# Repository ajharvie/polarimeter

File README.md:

Firmware and supporting data for a polarimeter as described in Scientific Reports: **A high-resolution polarimeter formed from inexpensive optical parts** https://doi.org/10.1038/s41598-020-61715-7

Code for the microcontroller can be found in the "Arduino Code" folder. The folder "Frontend tool" provides a simple python GUI for interfacing with the polarimeter. 
"Design files" contains .stl format files for custom parts used to build the polarimeter, as well as .brd files for circuit boards.
"Supporting Files" contains code for recording optical signals and simulating polarimeter behaviour, as well as data files for the plots presented in the paper.

*A.J. Harvie, T.W. Phillips and J.C. deMello*

**A new version - OPol - has been released. You can find the design files here: https://github.com/OpenPolarimeter/OPol, and a publication describing its build and use here: https://doi.org/10.1002/cmtd.202000057**

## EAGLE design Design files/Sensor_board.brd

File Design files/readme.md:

Design files for custom parts for the polarimeter, including:

1) .stl format files for the flow cell and mounting block
2) .stl format file for the 3d printed part for mounting the optical sensors onto an optical post
3) .brd and .sch files for a PCB to interface with the OPT101s (use of 8-pin DIP sockets recommended)
4) .stl format file for the 3d printed part for mounting the microcontroller
5) .brd and .sch files for a PCB for connections to the µC (and power passthrough)
6) A technical drawing of the flow cell dimensions

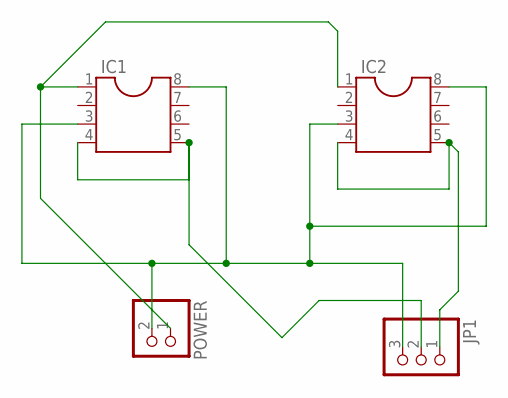
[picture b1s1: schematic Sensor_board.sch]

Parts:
IC1, IC2: DIL8S; SOCKET-08
JP1: PINHD-1X3; 1X03
POWER: PINHD-1X2; 1X02

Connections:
unnamed: IC1.3, IC1.8, IC2.3, IC2.8, JP1.3, POWER.2
unnamed: IC1.1, IC2.1, POWER.1
unnamed: IC1.4, IC1.5, JP1.2
unnamed: IC2.4, IC2.5, JP1.1

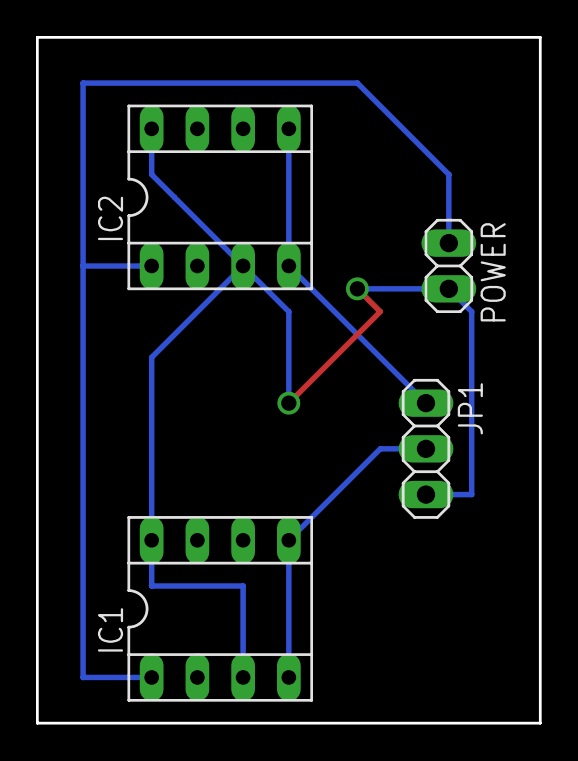
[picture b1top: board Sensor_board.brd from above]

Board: 2 copper layers, 27.9 x 38.1 mm, 4 parts (0 on the bottom side), 4 nets.

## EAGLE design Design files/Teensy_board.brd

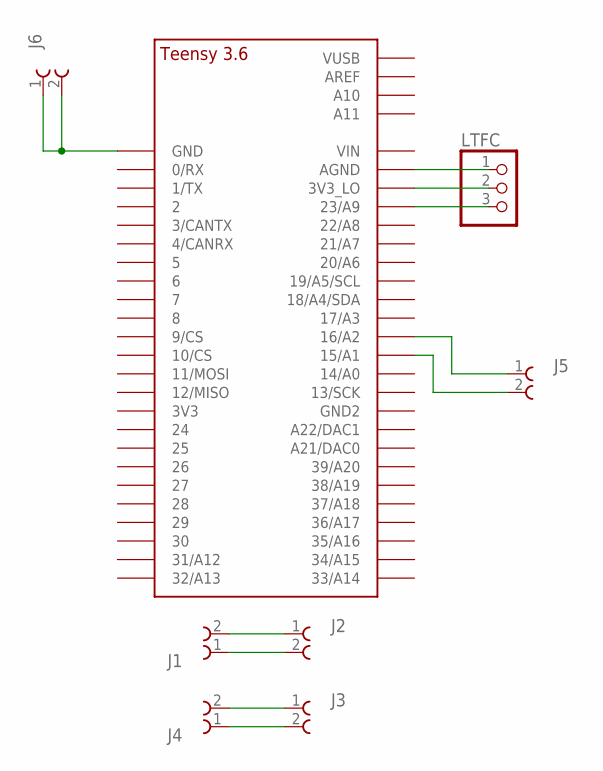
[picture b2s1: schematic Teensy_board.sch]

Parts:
J1, J2, J3, J4, J5, J6: 691103110002
LTFC: PINHD-1X3; 1X03
U$1: TEENSY_3.5/3.6_BASIC

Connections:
unnamed: LTFC.1, U$1.AGND
unnamed: LTFC.2, U$1.3V3_LO
unnamed: LTFC.3, U$1.23/A9
unnamed: J5.2, U$1.15/A1
unnamed: J5.1, U$1.16/A2
unnamed: J1.2, J2.1
unnamed: J1.1, J2.2
unnamed: J3.1, J4.2
unnamed: J3.2, J4.1
SIGNAL_G: J6.1, J6.2, U$1.GND

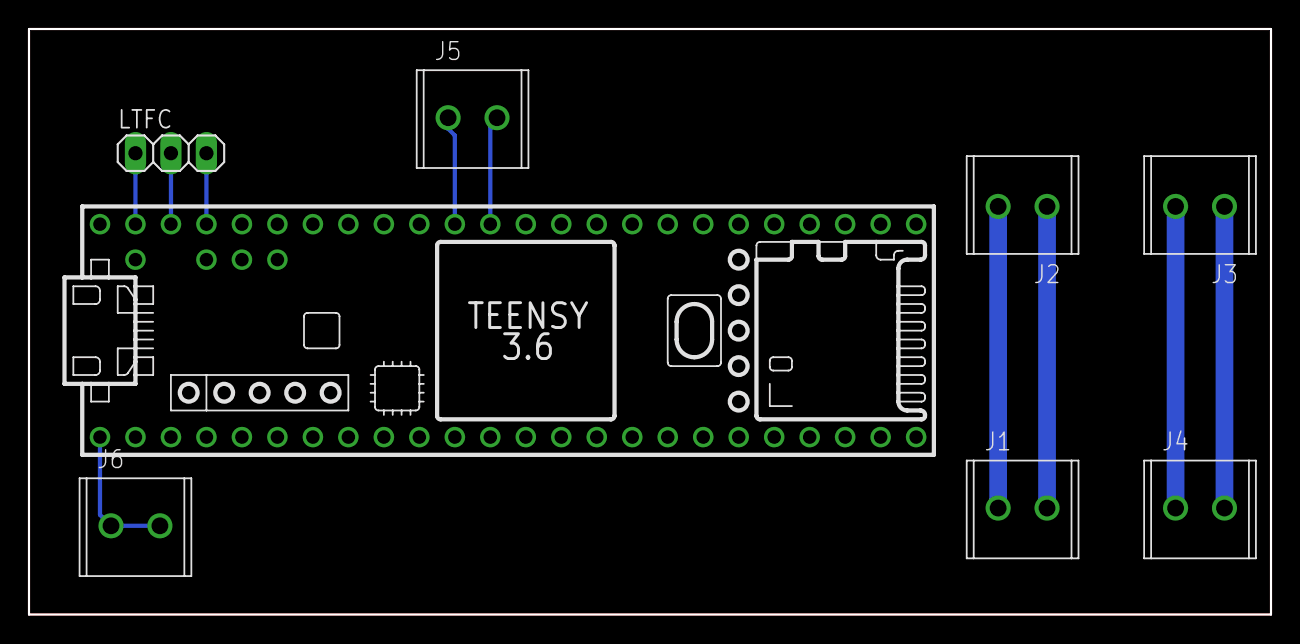
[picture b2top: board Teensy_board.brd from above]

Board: 2 copper layers, 88.9 x 41.9 mm, 8 parts (0 on the bottom side), 10 nets.

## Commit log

2019-10-31 removed unused variables
2020-02-10 Added code for recording of optical signals
2020-02-25 Create LICENSE
2020-02-27 added licence text
2020-03-05 added updated polarimeter firmware
    version is compatible with current (1.51) version of teensyduino
2020-03-05 Rename Teensy_Polarimeter.ino to TeensyPolarimeterv1_0.ino
2020-10-21 added link to new version to readme

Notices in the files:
parts and their libraries:
Wurth_Elektronik_Electromechanic_Termina: Copyright: Würth Elektronik
